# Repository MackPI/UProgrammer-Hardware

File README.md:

# UProgrammer-Hardware
Kicad Files for Universal programmer

Version J has updates for another spin of the PCB. 
Found errors and fixed them while checking the plots.

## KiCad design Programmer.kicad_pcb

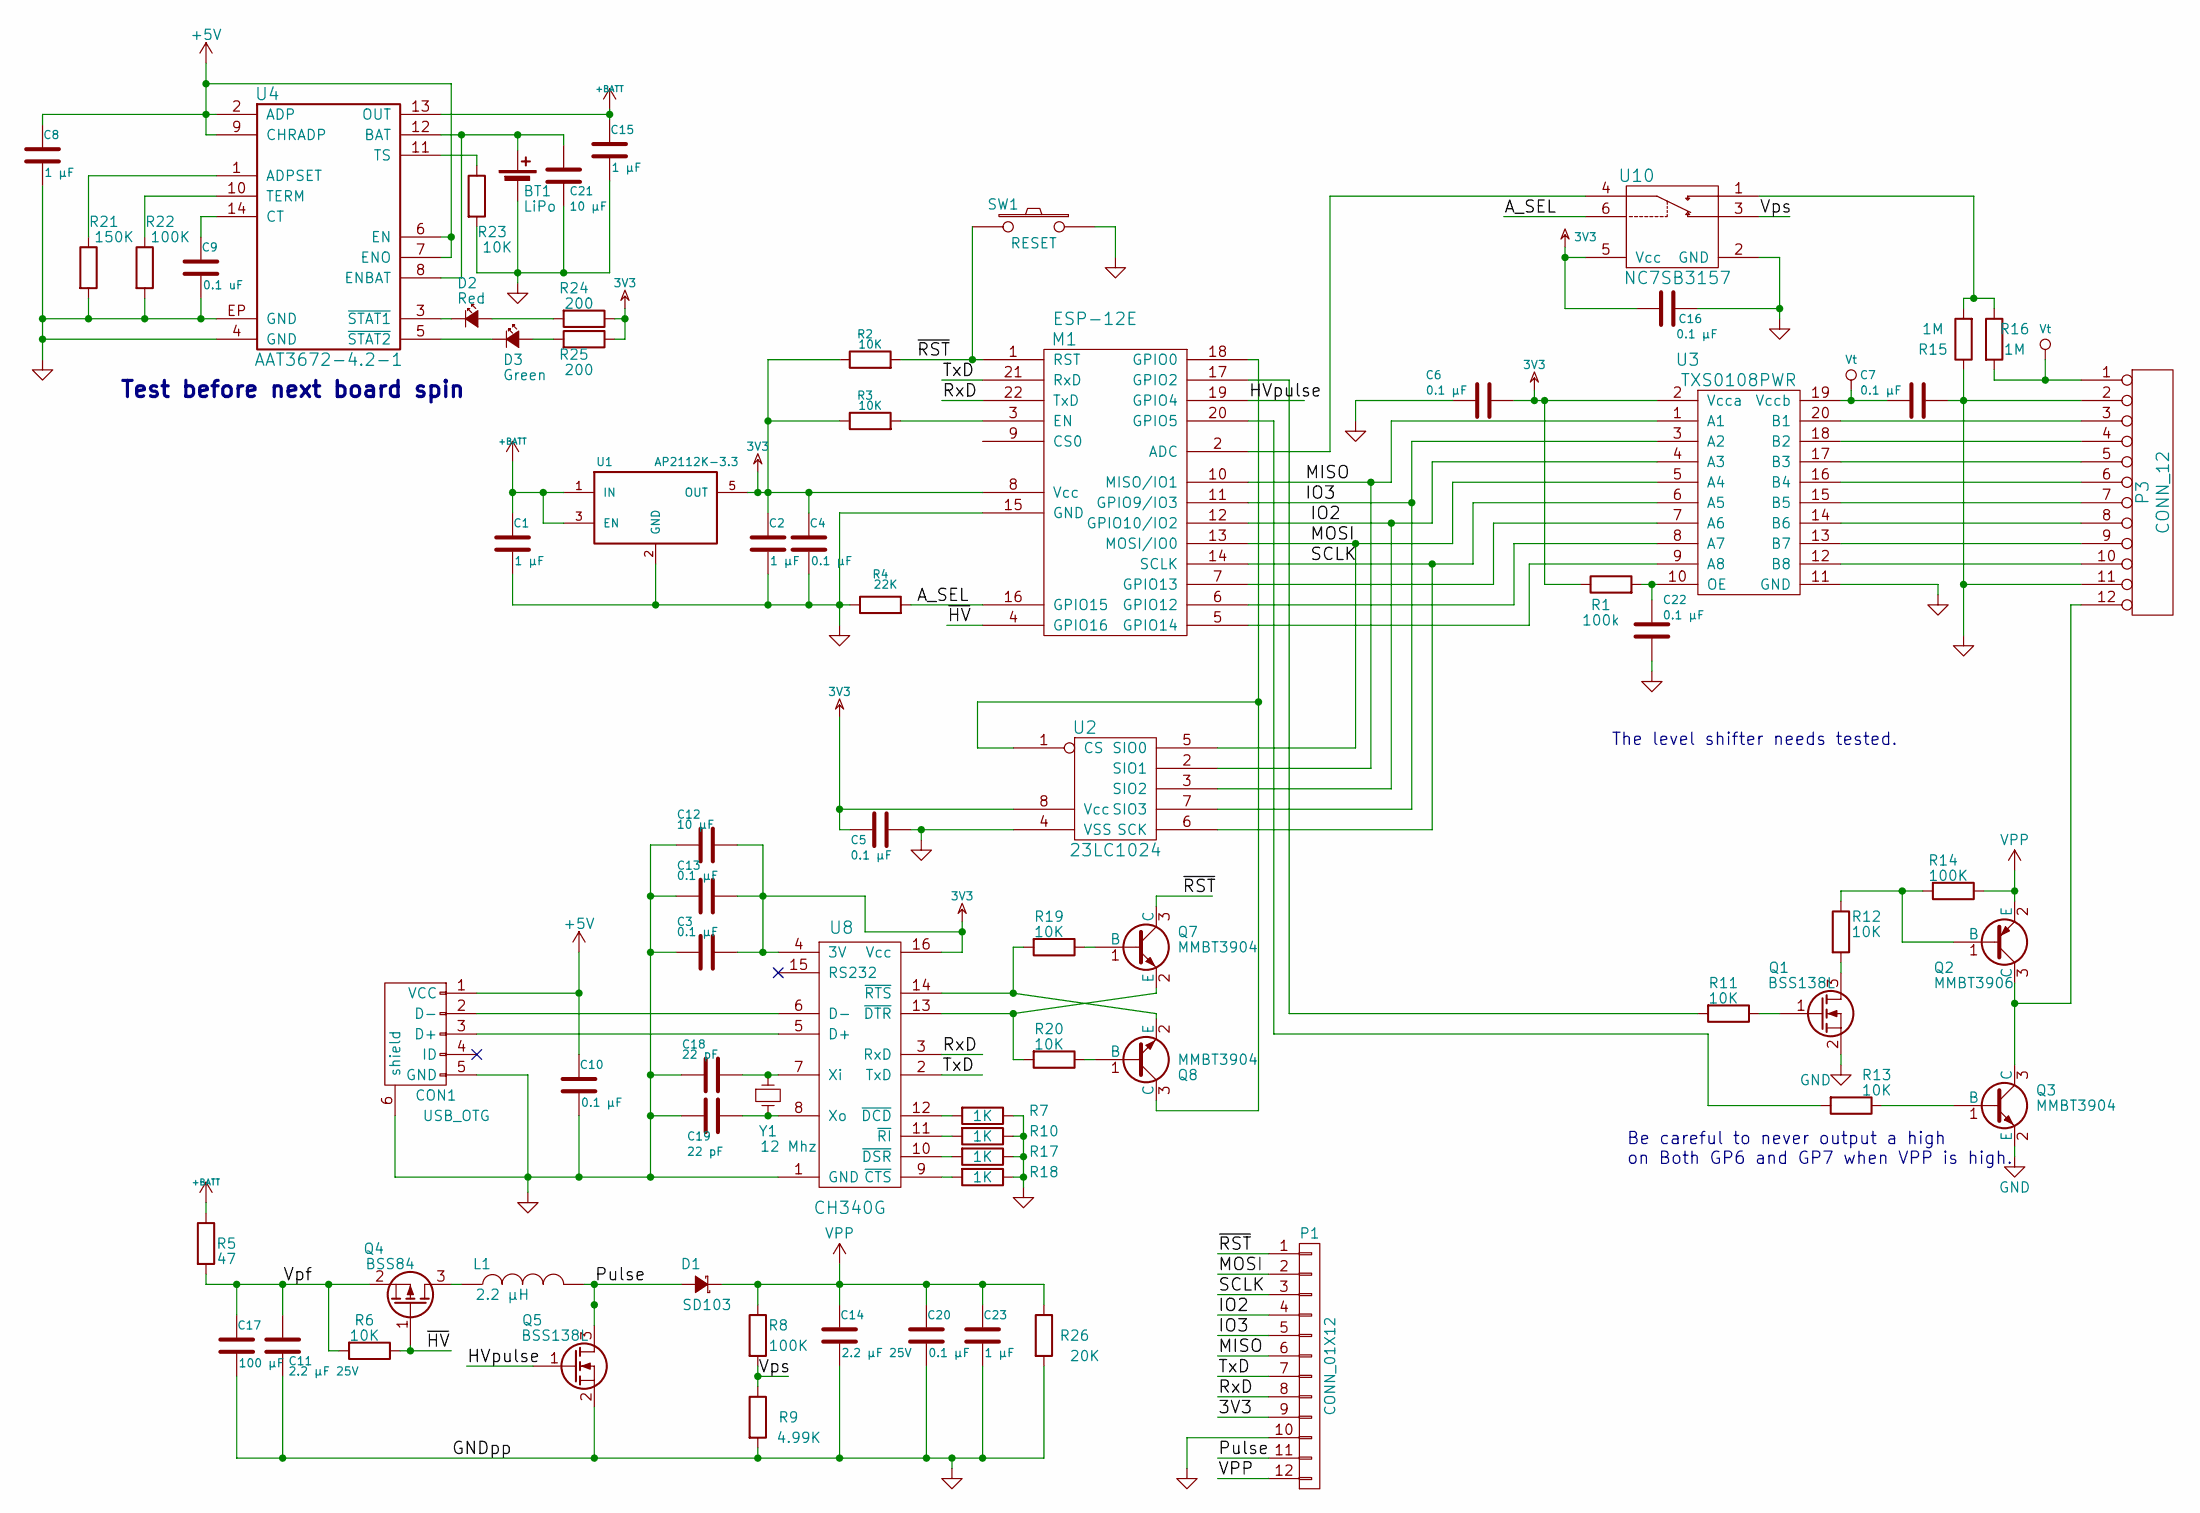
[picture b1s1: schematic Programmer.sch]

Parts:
BT1: LiPo; PINHEAD1-2
C1, C2, C8, C15, C23: 1 µF; C_1206
C3, C4, C5, C6, C7, C10, C13, C16, C20, C22: 0.1 µF; C_1206
C9: 0.1 uF; C_1206
C11, C14: 2.2 µF 25V; C_1206
C12, C21: 10 µF; C_1206
C17: 100 µF; C_1206
C18, C19: 22 pF; C_1206
CON1: USB_OTG; USB_Micro-B
D1: SD103; SOD-323
D2: Red; LED_1206
D3: Green; LED_1206
L1: 2.2 µH; Choke_SMD_1206_Standard
M1: ESP-12E
P1: CONN_01X12; Socket_Strip_Straight_1x12
P3: CONN_12; Pin_Header_Straight_2x06
Q1, Q5: BSS138L; SOT-23
Q2: MMBT3906; SOT-23
Q3, Q7, Q8: MMBT3904; SOT-23
Q4: BSS84; SOT-23
R1: 100k; R_1206
R2, R3, R6, R11, R12, R13, R19, R20, R23: 10K; R_1206
R4: 22K; R_1206
R5: 47; R_1206
R7, R10, R17, R18: 1K; R_1206
R8, R14, R22: 100K; R_1206
R9: 4.99K; R_1206
R15, R16: 1M; R_1206
R21: 150K; R_1206
R24, R25: 200; R_1206
R26: 20K; R_1206
SW1: RESET; R_1206
U1: AP2112K-3.3; SOT-23-5
U2: 23LC1024; SOIC-8_3.9x4.9mm_Pitch1.27mm
U3: TXS0108PWR; TSSOP-20_4.4x6.5mm_Pitch0.65mm
U4: AAT3672-4.2-1; DFN-14-1EP_3x3mm_Pitch0.4mm
U8: CH340G; SO-16-N
U10: NC7SB3157; SC-70-6
Y1: 12 Mhz; Crystal_HC49-SD_SMD; Digikey ABLS-12.000MHZ-B2-T

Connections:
3V3: C2.1, C3.1, C4.1, C5.2, C6.2, C12.1, C13.1, C16.1, M1.8 (Vcc), P1.9, R1.1, R2.1, R3.1, R24.1, R25.1, U1.5 (OUT), U2.8 (Vcc), U3.2 (Vcca), U8.4 (3V), U8.16 (Vcc), U10.5 (Vcc)
+5V: C8.1, C10.1, CON1.1 (VCC), U4.2 (ADP), U4.6 (EN), U4.7 (ENO), U4.9 (CHRADP)
+BATT: C1.1, C15.1, R5.1, U1.1 (IN), U1.3 (EN), U4.13 (OUT)
/A_SEL: M1.16 (GPIO15), R4.2, U10.6
/HVpulse: M1.19 (GPIO4), Q5.1 (G)
/IO2: M1.12 (GPIO10/IO2), P1.4, U2.3 (SIO2), U3.4 (A3)
/IO3: M1.11 (GPIO9/IO3), P1.5, U2.7 (SIO3), U3.3 (A2)
/MISO: M1.10 (MISO/IO1), P1.6, U2.2 (SIO1), U3.1 (A1)
/MOSI: M1.13 (MOSI/IO0), P1.2, U2.5 (SIO0), U3.5 (A4)
/Pulse: D1.2 (A), L1.2, P1.11, Q5.3 (D)
/RxD: M1.22 (TxD), P1.8, U8.3 (RxD)
/SCLK: M1.14 (SCLK), P1.3, U2.6 (SCK), U3.6 (A5)
/TxD: M1.21 (RxD), P1.7, U8.2 (TxD)
/Vpf: C11.1, C17.1, Q4.2 (S), R5.2, R6.2
/Vps: R8.2, R9.1, U10.3
/~HV: M1.4 (GPIO16), Q4.1 (G), R6.1
/~RST: M1.1 (RST), P1.1, Q7.3 (C), R2.2, SW1.2
GND: BT1.2, C1.2, C2.2, C3.2, C4.2, C5.1, C6.1, C7.2, C8.2, C9.2, C10.2, C11.2, C12.2, C13.2, C14.2, C15.2, C16.2, C17.2, C18.2, C19.2, C20.2, C21.2, C22.2, C23.2, CON1.5 (GND), CON1.6 (shield), M1.15 (GND), P1.10, P3.2, P3.11, Q1.2 (S), Q3.2 (E), Q5.2 (S), R4.1, R7.1, R9.2, R10.1, R15.1, R17.1, R18.1, R21.2, R22.2, R23.2, R26.2, SW1.1, U1.2 (GND), U2.4 (VSS), U3.11 (GND), U4.4 (GND), U4.EP (GND), U8.1 (GND), U10.2 (GND)
unnamed: BT1.1, C21.1, U4.8 (ENBAT), U4.12 (BAT)
unnamed: C9.1, U4.14 (CT)
unnamed: C18.1, U8.7 (Xi), Y1.1
unnamed: C19.1, U8.8 (Xo), Y1.2
unnamed: C22.1, R1.2, U3.10 (OE)
unnamed: CON1.2 (D-), U8.6 (D-)
unnamed: CON1.3 (D+), U8.5 (D+)
unnamed: D2.1 (K), U4.3 (~STAT1)
unnamed: D2.2 (A), R24.2
unnamed: D3.1 (K), U4.5 (~STAT2)
unnamed: D3.2 (A), R25.2
unnamed: L1.1, Q4.3 (D)
unnamed: M1.2 (ADC), U10.4
unnamed: M1.3 (EN), R3.2
unnamed: M1.5 (GPIO14), U3.9 (A8)
unnamed: M1.6 (GPIO12), U3.8 (A7)
unnamed: M1.7 (GPIO13), U3.7 (A6)
unnamed: M1.17 (GPIO2), R11.2
unnamed: M1.18 (GPIO0), Q8.3 (C), U2.1 (CS)
unnamed: M1.20 (GPIO5), R13.2
unnamed: P3.3, U3.20 (B1)
unnamed: P3.4, U3.18 (B2)
unnamed: P3.5, U3.17 (B3)
unnamed: P3.6, U3.16 (B4)
unnamed: P3.7, U3.15 (B5)
unnamed: P3.8, U3.14 (B6)
unnamed: P3.9, U3.13 (B7)
unnamed: P3.10, U3.12 (B8)
unnamed: P3.12, Q2.3 (C), Q3.3 (C)
unnamed: Q1.1 (G), R11.1
unnamed: Q1.3 (D), R12.2
unnamed: Q2.1 (B), R12.1, R14.2
unnamed: Q3.1 (B), R13.1
unnamed: Q7.1 (B), R19.1
unnamed: Q8.1 (B), R20.1
unnamed: R7.2, U8.12 (~DCD)
unnamed: R10.2, U8.11 (~RI)
unnamed: R15.2, R16.1, U10.1
unnamed: R17.2, U8.10 (~DSR)
unnamed: R18.2, U8.9 (~CTS)
unnamed: R21.1, U4.1 (ADPSET)
unnamed: R22.1, U4.10 (TERM)
unnamed: R23.1, U4.11 (TS)
VEE: C7.1, P3.1, R16.2, U3.19 (Vccb)
VPP: C14.1, C20.1, C23.1, D1.1 (K), P1.12, Q2.2 (E), R8.1, R14.1, R26.1

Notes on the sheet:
Be careful to never output a high on Both GP6 and GP7 when VPP is high.
The level shifter needs tested.
Test before next board spin

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
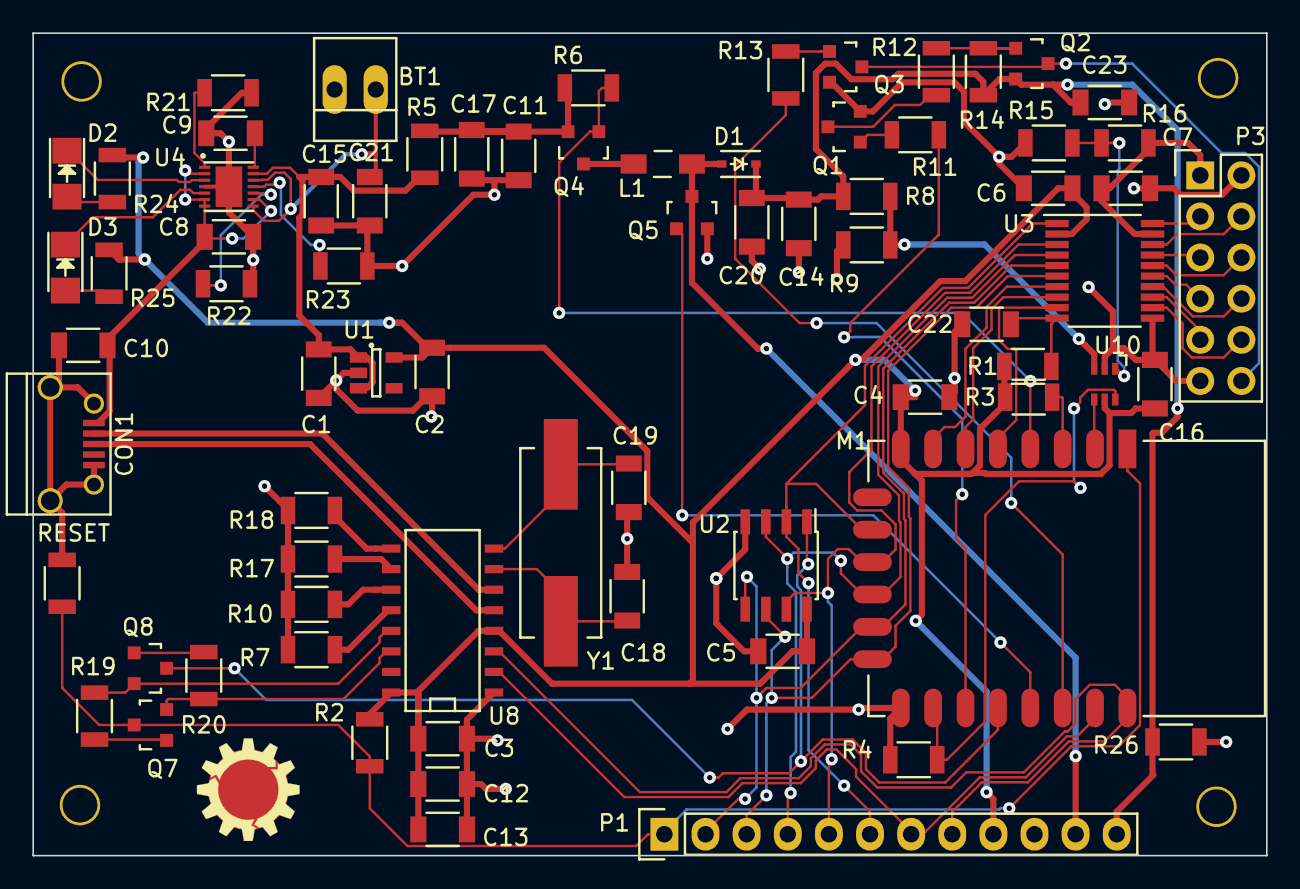
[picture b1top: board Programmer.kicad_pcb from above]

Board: 2 copper layers, 76.2 x 50.8 mm, 74 parts (0 on the bottom side), 65 nets.

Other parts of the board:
Ref**: Val**; PILogo1

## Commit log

2015-11-06 Version 00B of Schematic
    First Published version, Has not been through engineering review.
2015-11-13 Desing Review V00B
    Corrections made from doing a Design Review.
    Now at revision 00B
2015-11-20 Re-layout Update V00B
    Multiple changes to the schematic and PCB component placement, complete
    re-route of PCB.
2016-01-03 V00b PCB fixes
    Fixes needed to repair mistakes in PCB design.
2016-02-12 Hardware V00C
    Design Update to start testing a lithium polimer cell as my power
    source. Added a charge management IC that charges as well as supplies
    system voltage.
2016-02-19 Hardware V00D
    Revisions found during design review
2016-03-05 New Layout V00E
    Updated layout with newest schematic design.
2016-03-12 Hardware V00F
    BOM and Fabrication files
2016-07-09 Hardware V00G
    Changed value of R5 from 100 to 47 Ohms. This improves the voltage boost
    functionality.
2016-09-23 Hardware Version 00H
    Schematic updated to get ready for a new layout.
2016-09-30 Small change to Voltage Boost Circuit (Hardware V00I)
    Added a loading resistor and another filter capacitor to the Voltage
    boost Circuit. R26 and C23
2016-10-08 New Layout Hardware V00I
    Updated layout to match schematic in Version H. Ready to go to
    fabrication.
2016-10-15 Fixed errors found Hardware V00J
    Fixed DTR/RTS Lines and my logo on the board
2016-11-04 Minor Changes
2017-03-04 Hardware V00K
    Removed SPI RAM, Switched to HSPI only. Using FAN5331 for switching
    regulator. Some cleanup and re-labeling
2017-07-23 Multiple Level shifters instead of one
